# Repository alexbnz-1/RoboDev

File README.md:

# RoboDev

An open-source STM32-based robotics carrier board with integrated WiFi. Plug in power, plug in your motors and sensors — that's it. No breadboard, no stacked breakout boards, no wiring harness.

> **Status:** Schematic substantially complete · PCB layout not yet started

---

## Architecture

RoboDev uses a two-MCU design:

| | |
|---|---|
| **Primary MCU** | STM32G431RBTx · Cortex-M4F 170 MHz · motor control, real-time I/O |
| **WiFi co-processor** | ESP32-C3-MINI-1-N4 · SPI-connected · handles wireless comms |

---

## What's on the board

| | |
|---|---|
| **DC motors** | 4 channels · DRV8874PWPR · up to ~40 V · ~5 A cont. |
| **Servos** | 16 channels · PCA9685PW · 5 V servo rail |
| **Steppers** | 2× NEMA 17 · TMC2209-LA-T · StealthChop2 · silent operation |
| **CAN bus** | SN65HVD230D · ISO 11898-1 · screw terminal + 5.08 mm connector |
| **IMU** | BMI270 · 6-axis accel + gyro · SPI interface |
| **16-bit ADC** | ADS1115IDGST · 4-channel · I²C |
| **Native ADC** | 3× 2.54 mm headers · STM32 ADC |
| **GPIO expander** | PCF8574DW · 8 additional I/O · I²C |
| **Encoders** | 2 channels · 2.54 mm headers |
| **I²C expansion** | 16 independent ports · mix of QWIIC (JST SH) + 2.54 mm · 2× TCA9548APWR mux |
| **USB** | Type-C · USB4085-GF-A |
| **SWD debug** | 2.54 mm header |
| **UART** | 2× headers (debug + general) |
| **Power input** | XT60PW-M · reverse polarity protection · slide switch |

---

## Motor compatibility

| Motor | Works? | Notes |
|---|---|---|
| TT yellow gearmotors (2WD/4WD) | ✓ | Ideal fit |
| Pololu micro/mini gearmotors | ✓ | Well within limits |
| 25–37 mm DC gearmotors | ✓ | Software current limiting recommended near stall |
| Hobby servos | ✓ | Up to 16 channels via PCA9685 |
| NEMA 17 steppers | ✓ | TMC2209 · 2 A RMS / 2.8 A peak |
| CAN motor controllers (VESC, ODrive) | ✓ | Via SN65HVD230D CAN transceiver |
| 775-size / high-current motors | ✗ | Exceeds DRV8874 — use an external driver |

---

## Power

Five independent rails from a single XT60 input with reverse polarity protection (IRF4905 P-channel MOSFET) and a slide switch.

```
XT60  →  IRF4905 (reverse protect)  →  slide switch
           ├── VMOT    adj. buck (XL4016)  →  DC motors
           ├── VSTEP   adj. buck (XL4016)  →  steppers
           ├── +5V     LM2596T-5           →  servo rail + USB
           └── +3V3    AP2112K-3.3 LDO     →  STM32 + ESP32-C3 + all logic
```

VMOT and VSTEP are separate adjustable bucks so DC motors and steppers can run at different voltages simultaneously.

---

## I²C expansion

16 independent I²C ports behind two TCA9548APWR mux ICs — at zero GPIO cost, sharing the existing I²C bus. Each port is an isolated bus segment, so you can connect multiple devices with the same address across different ports without conflict.

3 ports are QWIIC (JST SH), the rest are standard 2.54 mm 4-pin headers. All carry GND / 3.3V / SDA / SCL.

---

## I²C address map

| Address | Device |
|---|---|
| 0x20 | PCF8574DW — digital GPIO expander |
| 0x3C | OLED display (user-supplied, optional) |
| 0x40 | PCA9685PW — 16-channel servo PWM |
| 0x48 | ADS1115IDGST — 16-bit ADC |
| 0x70 | TCA9548A Mux #1 — expansion ports 0–7 |
| 0x71 | TCA9548A Mux #2 — expansion ports 8–15 |

> BMI270 IMU is on SPI (via ESP32-C3), not I²C.

---

## Schematic structure

The KiCad project uses a hierarchical multi-sheet design:

| Sheet | Contents |
|---|---|
| Root | Top-level interconnect, mounting holes |
| `power` | XT60 input, reverse protect, all buck converters, LDO |
| `stm32` | STM32G431RBTx, SN65HVD230D CAN, USB-C, SWD, UART, ADC headers, encoders |
| `spi_bus` | ESP32-C3-MINI-1-N4 WiFi module, BMI270 IMU, 74HC595 shift register |
| `i2c_bus` | TCA9548A ×2 muxes, ADS1115 ADC, PCF8574 GPIO expander, all I²C headers |
| `motor_dc` | DRV8874PWPR ×4, motor output terminals, fault LEDs |
| `motor_stepper` | TMC2209-LA-T ×2, stepper output terminals, UART config |
| `motor_servo` | PCA9685PW, 16-channel servo headers |

---

## Project status

- [x] Design spec complete
- [x] KiCad schematic — substantially complete (all major blocks drawn)
- [ ] PCB layout
- [ ] Bringup firmware (I²C scan, PWM test, CAN loopback, UART echo)
- [ ] TCA9548A reverse-ARP HAL
- [ ] BMI270 driver + sensor fusion
- [ ] TMC2209 UART config
- [ ] Full LCSC/Mouser BOM with pricing

---

## Bill of materials

Key ICs: STM32G431RBTx · ESP32-C3-MINI-1-N4 · DRV8874PWPR ×4 · TMC2209-LA-T ×2 · PCA9685PW · ADS1115IDGST · PCF8574DW · TCA9548APWR ×2 · SN65HVD230D · BMI270 · USB4085-GF-A · XL4016 ×2 · LM2596T-5 · AP2112K-3.3

---

## Repo structure

```
/
├── hardware/
│   └── Robodev/     KiCad project (schematic + PCB)
├── firmware/        ESP-IDF / STM32 firmware (not yet started)
├── docs/
│   ├── Datasheets/  Component datasheets
│   └── RoboDevDesignSpec.docx
└── README.md
```

---

## Contributing

This is an early-stage open hardware project — no PCB has been fabricated yet. If you want to follow along or contribute, the most useful things right now are:

- KiCad schematic review
- Firmware: STM32 HAL bringup, TCA9548A I²C mux driver, TMC2209 UART configuration
- ESP32-C3 SPI bridge firmware
- BMI270 SPI driver + Madgwick/Mahony filter

---

*STM32 + ESP32-C3 Integrated Robotics Carrier Board · May 2026*

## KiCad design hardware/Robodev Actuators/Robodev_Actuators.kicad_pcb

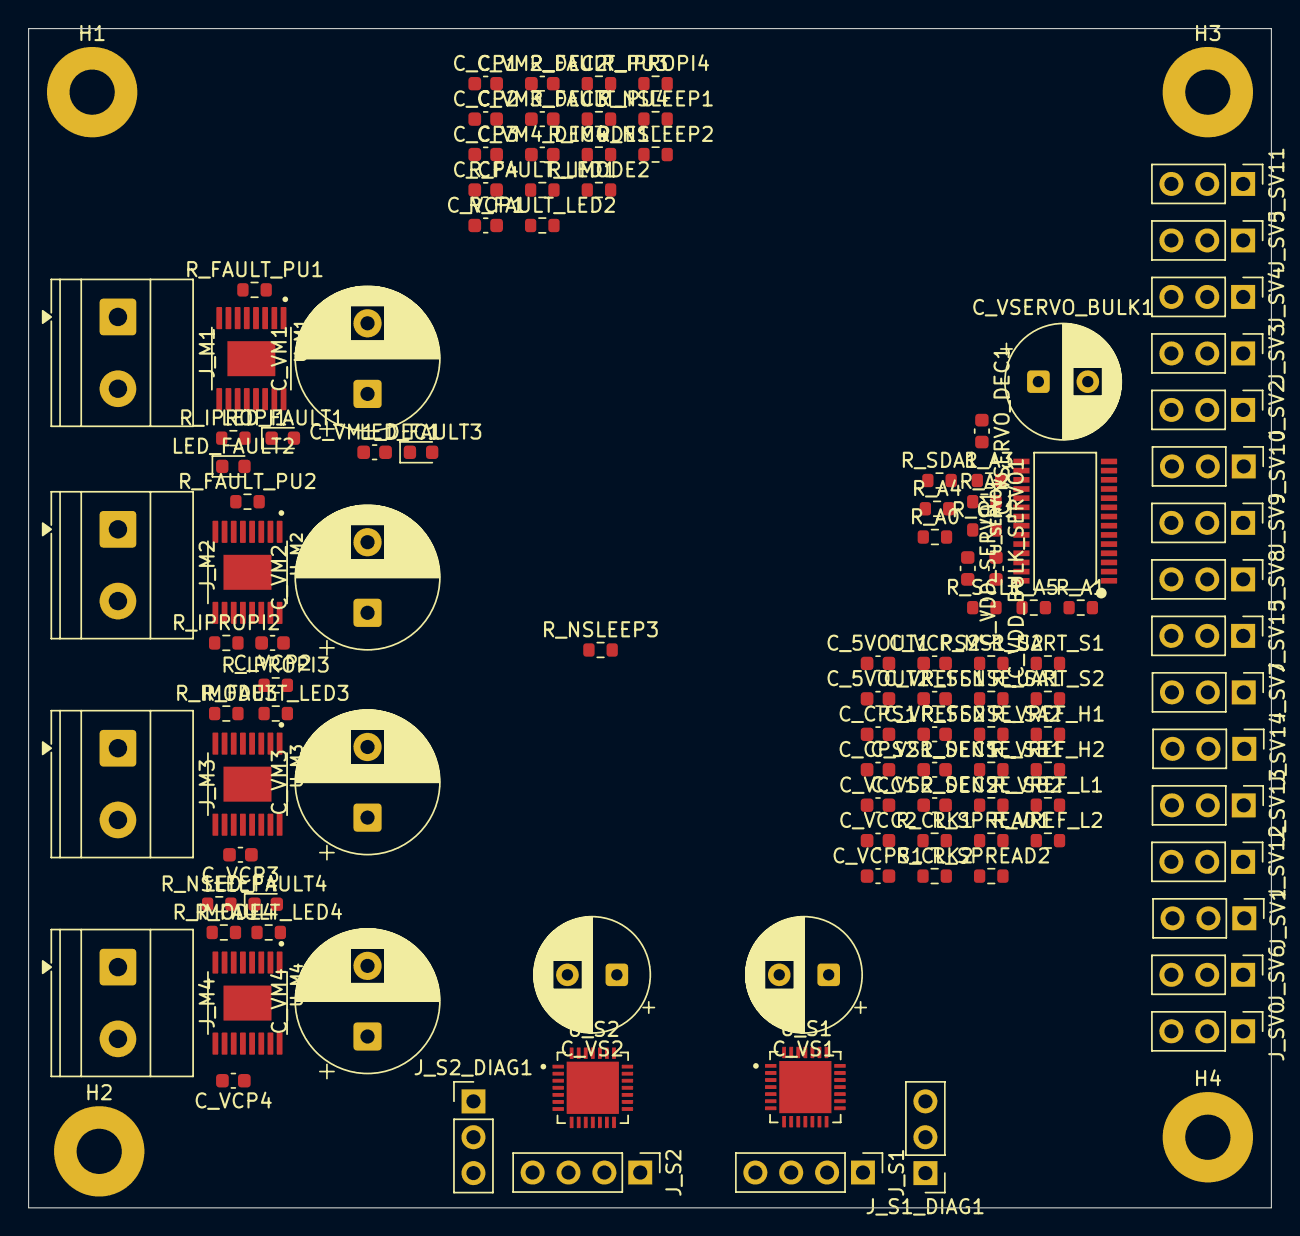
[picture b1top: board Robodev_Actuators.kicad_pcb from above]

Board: 4 copper layers, 88.0 x 83.5 mm, 117 parts (0 on the bottom side), 107 nets, no tracks yet.

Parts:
C_5VOUT1, C_5VOUT2: 4.7 µF 10V X5R; C_0603_1608Metric
C_CP1: 22nF 50V X7R; C_0603_1608Metric
C_CP2, C_CP3, C_CP4: 22 nF 50V X7R; C_0603_1608Metric
C_CPS1, C_CPS2: 100 nF 50V X7R; C_0603_1608Metric
C_VCC1, C_VCC2: 100 nF 10V X7R; C_0603_1608Metric
C_VCP1, C_VCP2, C_VCP3, C_VCP4: 100 nF 50V X7R; C_0603_1608Metric
C_VCPS1, C_VCPS2: 100 nF 50V X7R; C_0603_1608Metric
C_VDD_BULK_SERVO1: 10 µF 10V X5R; C_0603_1608Metric
C_VDD_SERVO1: 100 nF 10V X7R; C_0603_1608Metric
C_VM1, C_VM2, C_VM3, C_VM4: 470 µF 50V electrolytic; CP_Radial_D10.0mm_P5.00mm
C_VM1_DEC1, C_VM2_DEC2, C_VM3_DEC3, C_VM4_DEC4: 100 nF 50V X7R; C_0603_1608Metric
C_VREFS1, C_VREFS2: 100 nF 10V X7R; C_0603_1608Metric
C_VS1, C_VS2: 100 µF 50V electrolytic; CP_Radial_D8.0mm_P3.50mm
C_VS1_DEC1, C_VS2_DEC2: 100 nF 50V X7R; C_0603_1608Metric
C_VSERVO_BULK1: 220 µF 25V electrolytic; CP_Radial_D8.0mm_P3.50mm
C_VSERVO_DEC1: 100 nF 50V X7R; C_0603_1608Metric
H1, H2, H3, H4: MountingHole_Pad; MountingHole_3.2mm_M3_Pad
J_M1, J_M2, J_M3, J_M4: Conn_01x02; TerminalBlock_Phoenix_MKDS-1,5-2-5.08_1x02_P5.08mm_Horizont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
J_S1, J_S2: Stepper 4-pin 2.54mm; PinHeader_1x04_P2.54mm_Vertical
J_S1_DIAG1: Stepper 1 DIAG/INDEX; PinHeader_1x03_P2.54mm_Vertical
J_S2_DIAG1: Stepper 2 DIAG/INDEX; PinHeader_1x03_P2.54mm_Vertical
J_SV0, J_SV1, J_SV2, J_SV3, J_SV4, J_SV5, J_SV6, J_SV7, J_SV8, J_SV9, J_SV10, J_SV11, J_SV12, J_SV13, J_SV14, J_SV15: Conn_01x03; PinHeader_1x03_P2.54mm_Vertical
LED_FAULT1, LED_FAULT2, LED_FAULT3, LED_FAULT4: LTST-C190KRKT Red; LED_0603_1608Metric
R_A0, R_A1, R_A2, R_A3, R_A4, R_A5: 100 kΩ 1% 0603; R_0603_1608Metric
R_CLK1, R_CLK2: 100 kΩ 1% 0603; R_0603_1608Metric
R_FAULT_LED1, R_FAULT_LED2, R_FAULT_LED3, R_FAULT_LED4: 1 kΩ 1% 0603; R_0603_1608Metric
R_FAULT_PU1, R_FAULT_PU2, R_FAULT_PU3, R_FAULT_PU4: 10 kΩ 1% 0603; R_0603_1608Metric
R_IMODE1, R_IMODE2, R_IMODE3, R_IMODE4: 20 kΩ 1% 0603; R_0603_1608Metric
R_IPROPI1, R_IPROPI2, R_IPROPI3, R_IPROPI4: 1 kΩ 1% 0603; R_0603_1608Metric
R_MS1_S2: 10 kΩ 1% 0603; R_0603_1608Metric
R_NSLEEP1, R_NSLEEP2, R_NSLEEP3, R_NSLEEP4: 100 kΩ 1% 0603; R_0603_1608Metric
R_OE1: 100 kΩ 1% 0603; R_0603_1608Metric
R_SCL1: 4.7 kΩ 1% 0603; R_0603_1608Metric
R_SDA1: 4.7 kΩ 1% 0603; R_0603_1608Metric
R_SENSE_SA1, R_SENSE_SA2: 100 mΩ 1% 0603; R_0603_1608Metric
R_SENSE_SB1, R_SENSE_SB2: 100 mΩ 1% 0603; R_0603_1608Metric
R_SPREAD1, R_SPREAD2: 100 kΩ 1% 0603; R_0603_1608Metric
R_UART_S1, R_UART_S2: 1 kΩ 1% 0603; R_0603_1608Metric
R_VREF_H1, R_VREF_H2: 10 kΩ 1% 0603; R_0603_1608Metric
R_VREF_L1, R_VREF_L2: 27 kΩ 1% 0603; R_0603_1608Metric
U_M1, U_M2, U_M3, U_M4: DRV8874PWPR; SOP65P640X120-17N
U_S1, U_S2: TMC2209-LA-T; QFN50P500X500X90-29N
U_SERVO1: PCA9685PW; TSSOP28-0.65-9.7X4.4MM

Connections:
+3V3: C_VCC1.2, C_VCC2.2, C_VDD_BULK_SERVO1.2, C_VDD_SERVO1.2, R_FAULT_PU1.1, R_FAULT_PU2.1, R_FAULT_PU3.1, R_FAULT_PU4.1, R_MS1_S2.1, R_NSLEEP1.1, R_NSLEEP2.1, R_NSLEEP3.1, R_NSLEEP4.1, R_SCL1.1, R_SDA1.1, R_VREF_H1.1, R_VREF_H2.1, U_M1.5 (VREF), U_M2.5 (VREF), U_M3.5 (VREF), U_M4.5 (VREF), U_S1.15 (VCC_IO), U_S2.15 (VCC_IO), U_SERVO1.28 (VDD)
/motor_dc/IPROPI_M1: R_IPROPI1.1, U_M1.6 (IPROPI)
/motor_dc/IPROPI_M2: R_IPROPI2.1, U_M2.6 (IPROPI)
/motor_dc/IPROPI_M3: R_IPROPI3.1, U_M3.6 (IPROPI)
/motor_dc/IPROPI_M4: R_IPROPI4.1, U_M4.6 (IPROPI)
/motor_dc/VMOT: C_VCP1.2, C_VCP2.2, C_VCP3.2, C_VCP4.2, C_VM1.1, C_VM1_DEC1.1, C_VM2.1, C_VM2_DEC2.1, C_VM3.1, C_VM3_DEC3.1, C_VM4.1, C_VM4_DEC4.1, U_M1.11 (VM), U_M2.11 (VM), U_M3.11 (VM), U_M4.11 (VM)
/motor_servo/I2C_SCL: R_SCL1.2, U_SERVO1.26 (SCL)
/motor_servo/I2C_SDA: R_SDA1.2, U_SERVO1.27 (SDA)
/motor_servo/SV_PWM0: J_SV0.3, U_SERVO1.6 (LED0)
/motor_servo/SV_PWM1: J_SV1.3, U_SERVO1.7 (LED1)
/motor_servo/SV_PWM2: J_SV2.3, U_SERVO1.8 (LED2)
/motor_servo/SV_PWM3: J_SV3.3, U_SERVO1.9 (LED3)
/motor_servo/SV_PWM4: J_SV4.3, U_SERVO1.10 (LED4)
/motor_servo/SV_PWM5: J_SV5.3, U_SERVO1.11 (LED5)
/motor_servo/SV_PWM6: J_SV6.3, U_SERVO1.12 (LED6)
/motor_servo/SV_PWM7: J_SV7.3, U_SERVO1.13 (LED7)
/motor_servo/SV_PWM8: J_SV8.3, U_SERVO1.15 (LED8)
/motor_servo/SV_PWM9: J_SV9.3, U_SERVO1.16 (LED9)
/motor_servo/SV_PWM10: J_SV10.3, U_SERVO1.17 (LED10)
/motor_servo/SV_PWM11: J_SV11.3, U_SERVO1.18 (LED11)
/motor_servo/SV_PWM12: J_SV12.3, U_SERVO1.19 (LED12)
/motor_servo/SV_PWM13: J_SV13.3, U_SERVO1.20 (LED13)
/motor_servo/SV_PWM14: J_SV14.3, U_SERVO1.21 (LED14)
/motor_servo/SV_PWM15: J_SV15.3, U_SERVO1.22 (LED15)
/motor_stepper/S1_VREF: C_VREFS1.1, R_VREF_H1.2, R_VREF_L1.1, U_S1.17 (VREF)
/motor_stepper/S2_VREF: C_VREFS2.1, R_VREF_H2.2, R_VREF_L2.1, U_S2.17 (VREF)
/motor_stepper/TMC_UART: R_UART_S1.1, R_UART_S2.1
GND: C_5VOUT1.2, C_5VOUT2.2, C_VCC1.1, C_VCC2.1, C_VDD_BULK_SERVO1.1, C_VDD_SERVO1.1, C_VM1.2, C_VM1_DEC1.2, C_VM2.2, C_VM2_DEC2.2, C_VM3.2, C_VM3_DEC3.2, C_VM4.2, C_VM4_DEC4.2, C_VREFS1.2, C_VREFS2.2, H1.1, H2.1, H3.1, H4.1, J_S1_DIAG1.1, J_S2_DIAG1.1, LED_FAULT1.1 (K), LED_FAULT2.1 (K), LED_FAULT3.1 (K), LED_FAULT4.1 (K), R_A0.1, R_A1.1, R_A2.1, R_A3.1, R_A4.1, R_A5.1, R_CLK1.1, R_CLK2.1, R_IMODE1.1, R_IMODE2.1, R_IMODE3.1, R_IMODE4.1, R_IPROPI1.2, R_IPROPI2.2, R_IPROPI3.2, R_IPROPI4.2, R_OE1.1, R_SPREAD1.1, R_SPREAD2.1, R_VREF_L1.2, R_VREF_L2.2, U_M1.16 (PMODE), U_M2.16 (PMODE), U_M3.16 (PMODE), U_M4.16 (PMODE), U_S1.9 (MS1_AD0), U_S1.10 (MS2_AD1), U_S2.10 (MS2_AD1), U_SERVO1.14 (VSS), U_SERVO1.25 (EXTCLK)
MGND: U_M1.9 (PGND), U_M1.15 (GND), U_M2.9 (PGND), U_M2.15 (GND), U_M3.9 (PGND), U_M3.15 (GND), U_M4.9 (PGND), U_M4.15 (GND)
unnamed: J_M1.1, U_M1.8 (OUT1)
unnamed: J_M1.2, U_M1.10 (OUT2)
unnamed: J_M2.1, U_M2.8 (OUT1)
unnamed: J_M2.2, U_M2.10 (OUT2)
unnamed: J_M3.1, U_M3.8 (OUT1)
unnamed: J_M3.2, U_M3.10 (OUT2)
unnamed: J_M4.1, U_M4.8 (OUT1)
unnamed: J_M4.2, U_M4.10 (OUT2)
unnamed: J_S1.1, U_S1.24 (OA1)
unnamed: J_S1.2, U_S1.21 (OA2)
unnamed: J_S1.3, U_S1.26 (OB1)
unnamed: J_S1.4, U_S1.1 (OB2)
unnamed: J_S1_DIAG1.2, U_S1.11 (DIAG)
unnamed: J_S1_DIAG1.3, U_S1.12 (INDEX)
unnamed: J_S2.1, U_S2.24 (OA1)
unnamed: J_S2.2, U_S2.21 (OA2)
unnamed: J_S2.3, U_S2.26 (OB1)
unnamed: J_S2.4, U_S2.1 (OB2)
unnamed: J_S2_DIAG1.2, U_S2.11 (DIAG)
unnamed: J_S2_DIAG1.3, U_S2.12 (INDEX)
unnamed: LED_FAULT1.2 (A), R_FAULT_LED1.2
unnamed: LED_FAULT2.2 (A), R_FAULT_LED2.2
unnamed: LED_FAULT3.2 (A), R_FAULT_LED3.2
unnamed: LED_FAULT4.2 (A), R_FAULT_LED4.2
unnamed: C_CP1.1, U_M1.13 (CPH)
unnamed: C_CP1.2, U_M1.14 (CPL)
unnamed: R_IMODE1.2, U_M1.7 (IMODE)
unnamed: R_FAULT_LED1.1, R_FAULT_PU1.2, U_M1.4 (NFAULT)
unnamed: R_NSLEEP1.2, U_M1.3 (NSLEEP)
unnamed: C_VCP1.1, U_M1.12 (VCP)
unnamed: C_CP2.1, U_M2.13 (CPH)
unnamed: C_CP2.2, U_M2.14 (CPL)
unnamed: R_IMODE2.2, U_M2.7 (IMODE)
unnamed: R_FAULT_LED2.1, R_FAULT_PU2.2, U_M2.4 (NFAULT)
unnamed: R_NSLEEP2.2, U_M2.3 (NSLEEP)
unnamed: C_VCP2.1, U_M2.12 (VCP)
unnamed: C_CP3.1, U_M3.13 (CPH)
unnamed: C_CP3.2, U_M3.14 (CPL)
unnamed: R_IMODE3.2, U_M3.7 (IMODE)
unnamed: R_FAULT_LED3.1, R_FAULT_PU3.2, U_M3.4 (NFAULT)
unnamed: R_NSLEEP3.2, U_M3.3 (NSLEEP)
unnamed: C_VCP3.1, U_M3.12 (VCP)
unnamed: C_CP4.1, U_M4.13 (CPH)
unnamed: C_CP4.2, U_M4.14 (CPL)
unnamed: R_IMODE4.2, U_M4.7 (IMODE)
unnamed: R_FAULT_LED4.1, R_FAULT_PU4.2, U_M4.4 (NFAULT)
unnamed: R_NSLEEP4.2, U_M4.3 (NSLEEP)
unnamed: C_VCP4.1, U_M4.12 (VCP)
unnamed: C_5VOUT1.1, U_S1.8 (5VOUT)
unnamed: R_SENSE_SA1.1, U_S1.23 (BRA)
unnamed: R_SENSE_SB1.1, U_S1.27 (BRB)
unnamed: R_CLK1.2, U_S1.13 (CLK)
unnamed: C_CPS1.1, U_S1.5 (CPI)
unnamed: C_CPS1.2, U_S1.4 (CPO)
unnamed: R_SPREAD1.2, U_S1.7 (SPREAD)
unnamed: C_VCPS1.1, U_S1.6 (VCP)
unnamed: R_UART_S1.2, U_S1.14 (~PD_UART)
unnamed: C_5VOUT2.1, U_S2.8 (5VOUT)
unnamed: R_SENSE_SA2.1, U_S2.23 (BRA)
unnamed: R_SENSE_SB2.1, U_S2.27 (BRB)
unnamed: R_CLK2.2, U_S2.13 (CLK)
unnamed: C_CPS2.1, U_S2.5 (CPI)
unnamed: C_CPS2.2, U_S2.4 (CPO)
unnamed: R_MS1_S2.2, U_S2.9 (MS1_AD0)
unnamed: R_SPREAD2.2, U_S2.7 (SPREAD)
unnamed: C_VCPS2.1, U_S2.6 (VCP)
unnamed: R_UART_S2.2, U_S2.14 (~PD_UART)
unnamed: R_A0.2, U_SERVO1.1 (A0)
unnamed: R_A1.2, U_SERVO1.2 (A1)
unnamed: R_A2.2, U_SERVO1.3 (A2)
unnamed: R_A3.2, U_SERVO1.4 (A3)
unnamed: R_A4.2, U_SERVO1.5 (A4)
unnamed: R_A5.2, U_SERVO1.24 (A5)
unnamed: R_OE1.2, U_SERVO1.23 (~OE)
SERVOGND: C_VSERVO_BULK1.2, C_VSERVO_DEC1.2, J_SV0.1, J_SV1.1, J_SV2.1, J_SV3.1, J_SV4.1, J_SV5.1, J_SV6.1, J_SV7.1, J_SV8.1, J_SV9.1, J_SV10.1, J_SV11.1, J_SV12.1, J_SV13.1, J_SV14.1, J_SV15.1
STEPGND: C_VCPS1.2, C_VCPS2.2, C_VS1.2, C_VS1_DEC1.1, C_VS2.2, C_VS2_DEC2.1, R_SENSE_SA1.2, R_SENSE_SA2.2, R_SENSE_SB1.2, R_SENSE_SB2.2, U_S1.3 (GND), U_S2.3 (GND)
VS: C_VS1.1, C_VS1_DEC1.2, C_VS2.1, C_VS2_DEC2.2, U_S1.22 (VS), U_S1.28 (VS), U_S2.22 (VS), U_S2.28 (VS)
VSERVO: C_VSERVO_BULK1.1, C_VSERVO_DEC1.1, J_SV0.2, J_SV1.2, J_SV2.2, J_SV3.2, J_SV4.2, J_SV5.2, J_SV6.2, J_SV7.2, J_SV8.2, J_SV9.2, J_SV10.2, J_SV11.2, J_SV12.2, J_SV13.2, J_SV14.2, J_SV15.2

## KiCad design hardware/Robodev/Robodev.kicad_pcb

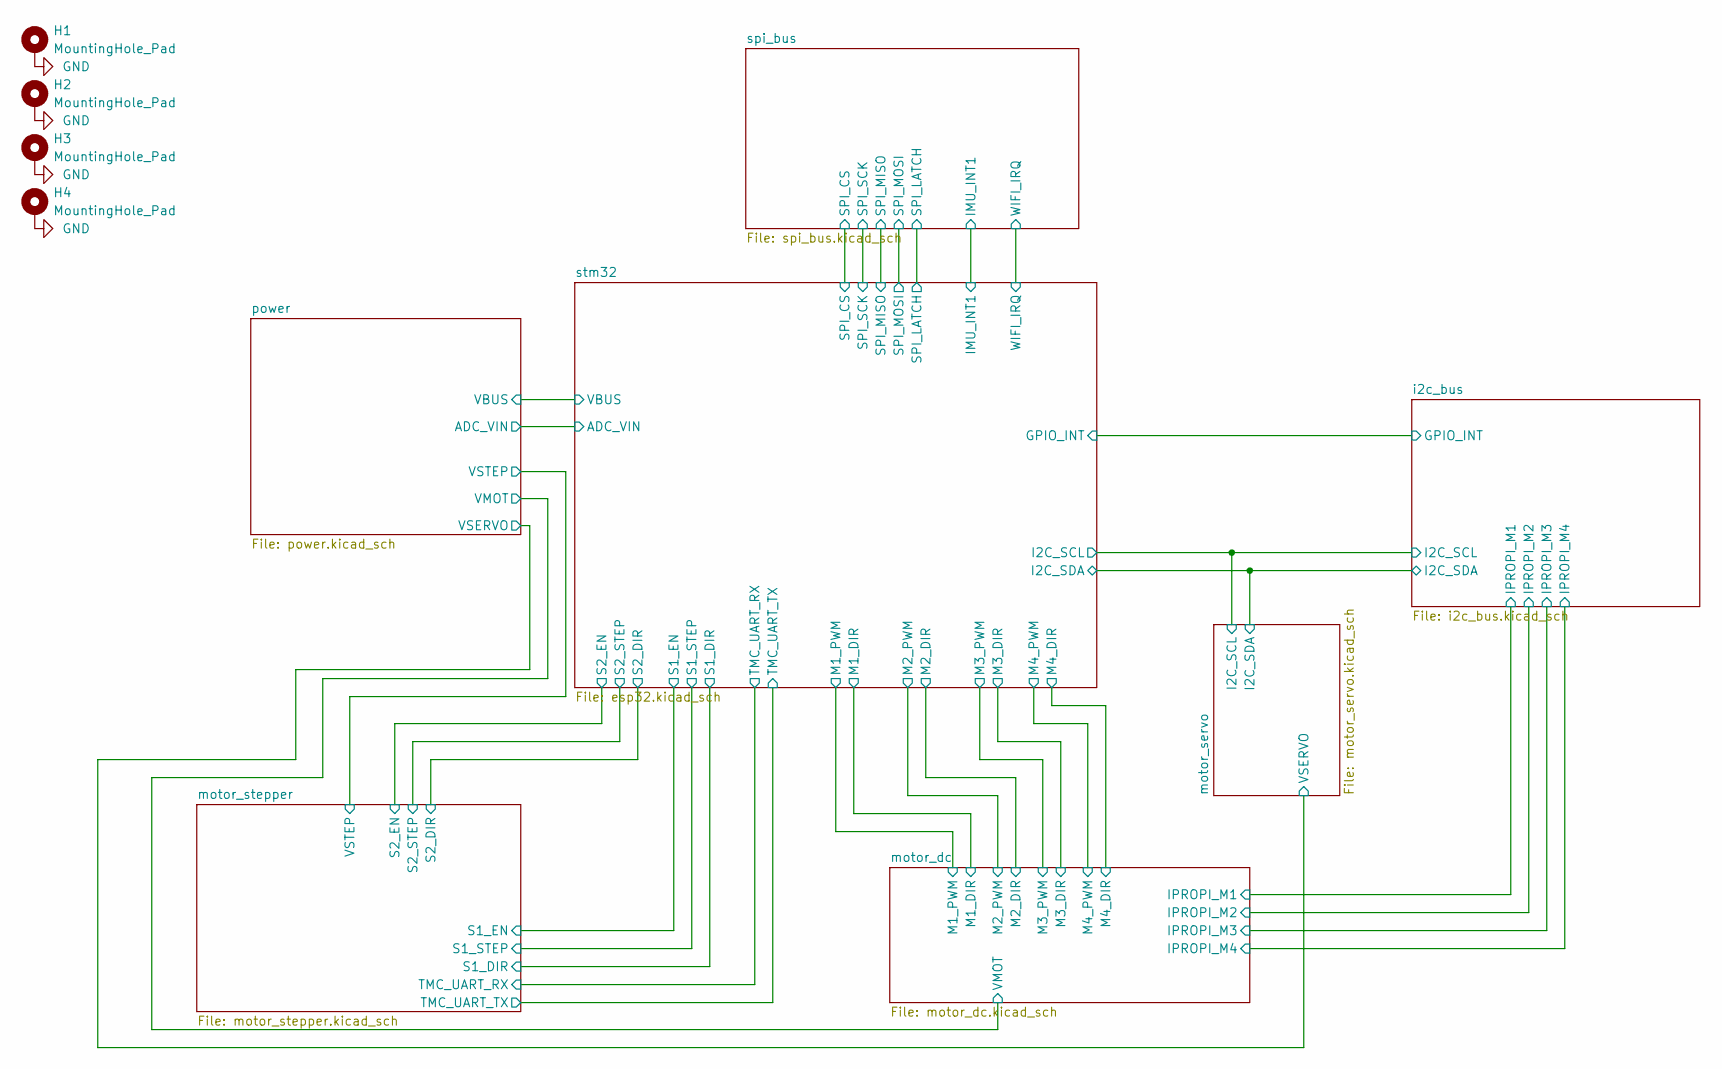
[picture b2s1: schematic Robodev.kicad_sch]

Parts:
H1, H2, H3, H4: MountingHole_Pad; MountingHole_3.2mm_M3_Pad

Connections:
GND: H1.1, H2.1, H3.1, H4.1; also elsewhere on the board

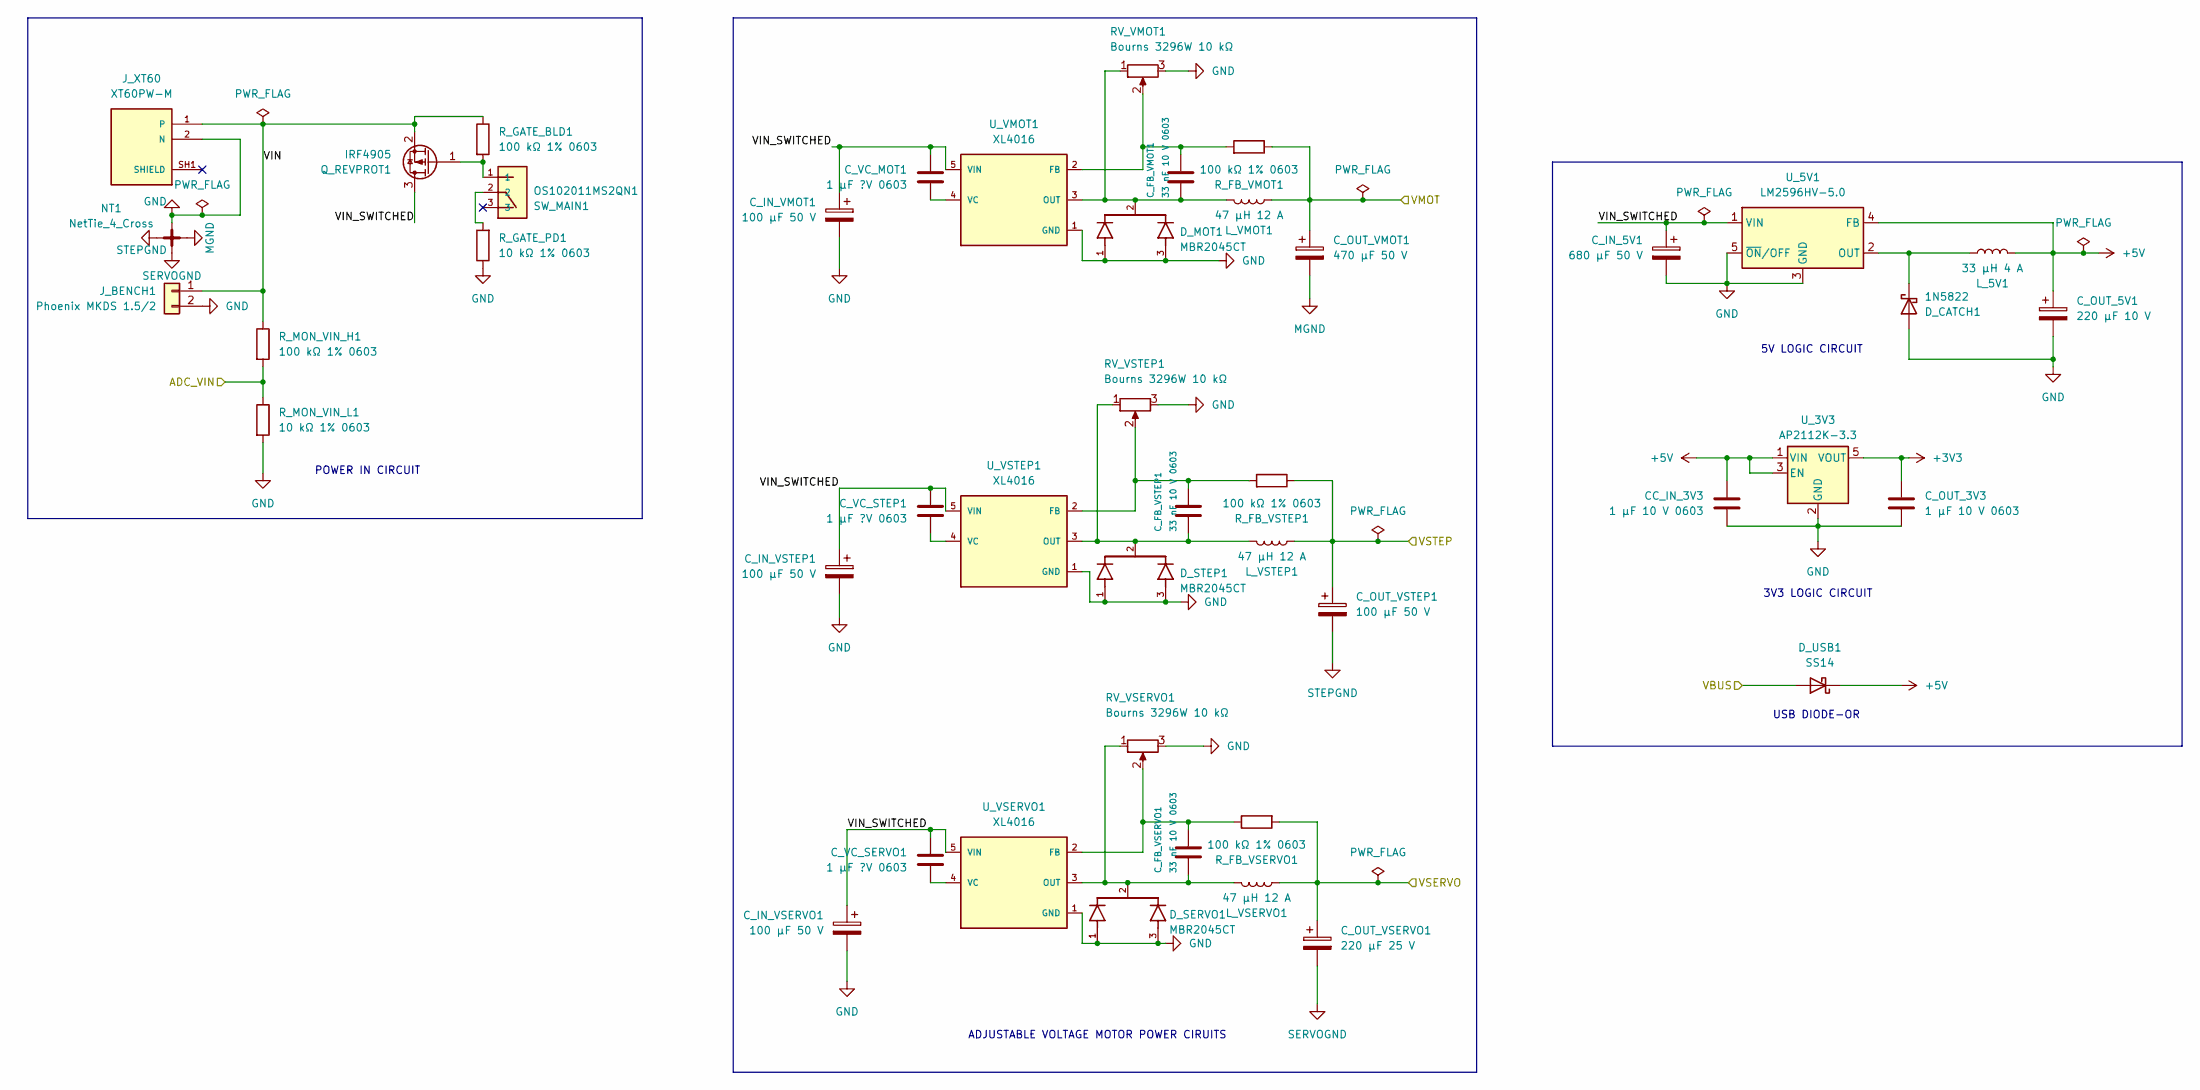
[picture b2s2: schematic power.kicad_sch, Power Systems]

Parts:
CC_IN_3V3: 1 µF 10 V 0603; C_0603_1608Metric
C_FB_VMOT1: 33 nF 10 V 0603; C_0603_1608Metric
C_FB_VSERVO1: 33 nF 10 V 0603; C_0603_1608Metric
C_FB_VSTEP1: 33 nF 10 V 0603; C_0603_1608Metric
C_IN_5V1: 680 µF 50 V; CP_Radial_D12.5mm_P5.00mm
C_IN_VMOT1: 100 µF 50 V; CP_Radial_D10.0mm_P5.00mm
C_IN_VSERVO1: 100 µF 50 V; CP_Radial_D10.0mm_P5.00mm
C_IN_VSTEP1: 100 µF 50 V; CP_Radial_D10.0mm_P5.00mm
C_OUT_3V3: 1 µF 10 V 0603; C_0603_1608Metric
C_OUT_5V1: 220 µF 10 V; CP_Radial_D8.0mm_P3.50mm
C_OUT_VMOT1: 470 µF 50 V; CP_Radial_D12.5mm_P5.00mm
C_OUT_VSERVO1: 220 µF 25 V; CP_Radial_D8.0mm_P3.50mm
C_OUT_VSTEP1: 100 µF 50 V; CP_Radial_D10.0mm_P5.00mm
C_VC_MOT1: 1 µF ?V 0603; C_0603_1608Metric
C_VC_SERVO1: 1 µF ?V 0603; C_0603_1608Metric
C_VC_STEP1: 1 µF ?V 0603; C_0603_1608Metric
D_CATCH1: 1N5822; D_DO-201AD_P12.70mm_Horizontal
D_MOT1: MBR2045CT; TO254P1050X476X2020-3; PARTREV G2104
D_SERVO1: MBR2045CT; TO254P1050X476X2020-3; PARTREV G2104
D_STEP1: MBR2045CT; TO254P1050X476X2020-3; PARTREV G2104
D_USB1: SS14; D_SMA
J_BENCH1: Phoenix MKDS 1.5/2; TerminalBlock_Phoenix_MKDS-1,5-2-5.08_1x02_P5.08mm_Horizont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
J_XT60: XT60PW-M; AMASS_XT60PW-M; PARTREV 1.2
L_5V1: 33 µH 4 A; L_Radial_D10.0mm_P5.00mm_Fastron_07M
L_VMOT1: 47 µH 12 A; L_Radial_D10.0mm_P5.00mm_Fastron_07M
L_VSERVO1: 47 µH 12 A; L_Radial_D10.0mm_P5.00mm_Fastron_07M
L_VSTEP1: 47 µH 12 A; L_Radial_D10.0mm_P5.00mm_Fastron_07M
NT1: NetTie_4_Cross; NetTie-4_SMD_Pad2.0mm
Q_REVPROT1: IRF4905; TO-220-3_Vertical
RV_VMOT1: Bourns 3296W 10 kΩ; Potentiometer_Bourns_3296W_Vertical
RV_VSERVO1: Bourns 3296W 10 kΩ; Potentiometer_Bourns_3296W_Vertical
RV_VSTEP1: Bourns 3296W 10 kΩ; Potentiometer_Bourns_3296W_Vertical
R_FB_VMOT1: 100 kΩ 1% 0603; R_0603_1608Metric
R_FB_VSERVO1: 100 kΩ 1% 0603; R_0603_1608Metric
R_FB_VSTEP1: 100 kΩ 1% 0603; R_0603_1608Metric
R_GATE_BLD1: 100 kΩ 1% 0603; R_0603_1608Metric
R_GATE_PD1: 10 kΩ 1% 0603; R_0603_1608Metric
R_MON_VIN_H1: 100 kΩ 1% 0603; R_0603_1608Metric
R_MON_VIN_L1: 10 kΩ 1% 0603; R_0603_1608Metric
SW_MAIN1: OS102011MS2QN1; SW_OS102011MS2QN1
U_3V3: AP2112K-3.3; SOT-23-5_HandSoldering
U_5V1: LM2596HV-5.0; TO-263-5_TabPin3
U_VMOT1: XL4016; LM2576T2
U_VSERVO1: XL4016; LM2576T2
U_VSTEP1: XL4016; LM2576T2

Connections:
+3V3: C_OUT_3V3.1, U_3V3.5 (VOUT); also elsewhere on the board
+5V: CC_IN_3V3.1, C_OUT_5V1.1, D_USB1.1 (K), L_5V1.1, U_3V3.1 (VIN), U_3V3.3 (EN), U_5V1.4 (FB)
/motor_dc/VMOT: C_OUT_VMOT1.1, L_VMOT1.2, R_FB_VMOT1.1; also elsewhere on the board
/power/ADC_VIN: R_MON_VIN_H1.2, R_MON_VIN_L1.1; also elsewhere on the board
/power/VIN: J_BENCH1.1, J_XT60.1, Q_REVPROT1.2 (S), R_GATE_BLD1.1, R_MON_VIN_H1.1
/power/VIN_SWITCHED: C_IN_5V1.1, C_IN_VMOT1.1, C_IN_VSERVO1.1, C_IN_VSTEP1.1, C_VC_MOT1.1, C_VC_SERVO1.1, C_VC_STEP1.1, Q_REVPROT1.3 (D), U_5V1.1 (VIN), U_VMOT1.5 (VIN), U_VSERVO1.5 (VIN), U_VSTEP1.5 (VIN)
GND: CC_IN_3V3.2, C_IN_5V1.2, C_IN_VMOT1.2, C_IN_VSERVO1.2, C_IN_VSTEP1.2, C_OUT_3V3.2, C_OUT_5V1.2, D_CATCH1.2 (A), D_MOT1.1, D_MOT1.3, D_SERVO1.1, D_SERVO1.3, D_STEP1.1, D_STEP1.3, J_BENCH1.2, J_XT60.2 (N), NT1.3, RV_VMOT1.3, RV_VSERVO1.3, RV_VSTEP1.3, R_GATE_PD1.1, R_MON_VIN_L1.2, U_3V3.2 (GND), U_5V1.3 (GND), U_5V1.5 (~ON/OFF), U_VMOT1.1 (GND), U_VSERVO1.1 (GND), U_VSTEP1.1 (GND); also elsewhere on the board
MGND: C_OUT_VMOT1.2, NT1.1; also elsewhere on the board
unnamed: D_CATCH1.1 (K), L_5V1.2, U_5V1.2 (OUT)
unnamed: Q_REVPROT1.1 (G), R_GATE_BLD1.2, SW_MAIN1.1
unnamed: R_GATE_PD1.2, SW_MAIN1.2
unnamed: C_FB_VMOT1.2, RV_VMOT1.2, R_FB_VMOT1.2, U_VMOT1.2 (FB)
unnamed: C_FB_VMOT1.1, D_MOT1.2, L_VMOT1.1, RV_VMOT1.1, U_VMOT1.3 (OUT)
unnamed: C_VC_MOT1.2, U_VMOT1.4 (VC)
unnamed: C_FB_VSERVO1.2, RV_VSERVO1.2, R_FB_VSERVO1.1, U_VSERVO1.2 (FB)
unnamed: C_FB_VSERVO1.1, D_SERVO1.2, L_VSERVO1.1, RV_VSERVO1.1, U_VSERVO1.3 (OUT)
unnamed: C_VC_SERVO1.2, U_VSERVO1.4 (VC)
unnamed: C_FB_VSTEP1.2, RV_VSTEP1.2, R_FB_VSTEP1.2, U_VSTEP1.2 (FB)
unnamed: C_FB_VSTEP1.1, D_STEP1.2, L_VSTEP1.2, RV_VSTEP1.1, U_VSTEP1.3 (OUT)
unnamed: C_VC_STEP1.2, U_VSTEP1.4 (VC)
SERVOGND: C_OUT_VSERVO1.2, NT1.4; also elsewhere on the board
STEPGND: C_OUT_VSTEP1.2, NT1.2; also elsewhere on the board
VBUS: D_USB1.2 (A); also elsewhere on the board
VS: C_OUT_VSTEP1.1, L_VSTEP1.1, R_FB_VSTEP1.1; also elsewhere on the board
VSERVO: C_OUT_VSERVO1.1, L_VSERVO1.2, R_FB_VSERVO1.2; also elsewhere on the board

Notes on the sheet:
USB DIODE-OR
3V3 LOGIC CIRCUIT
5V LOGIC CIRCUIT
POWER IN CIRCUIT
ADJUSTABLE VOLTAGE MOTOR POWER CIRUITS

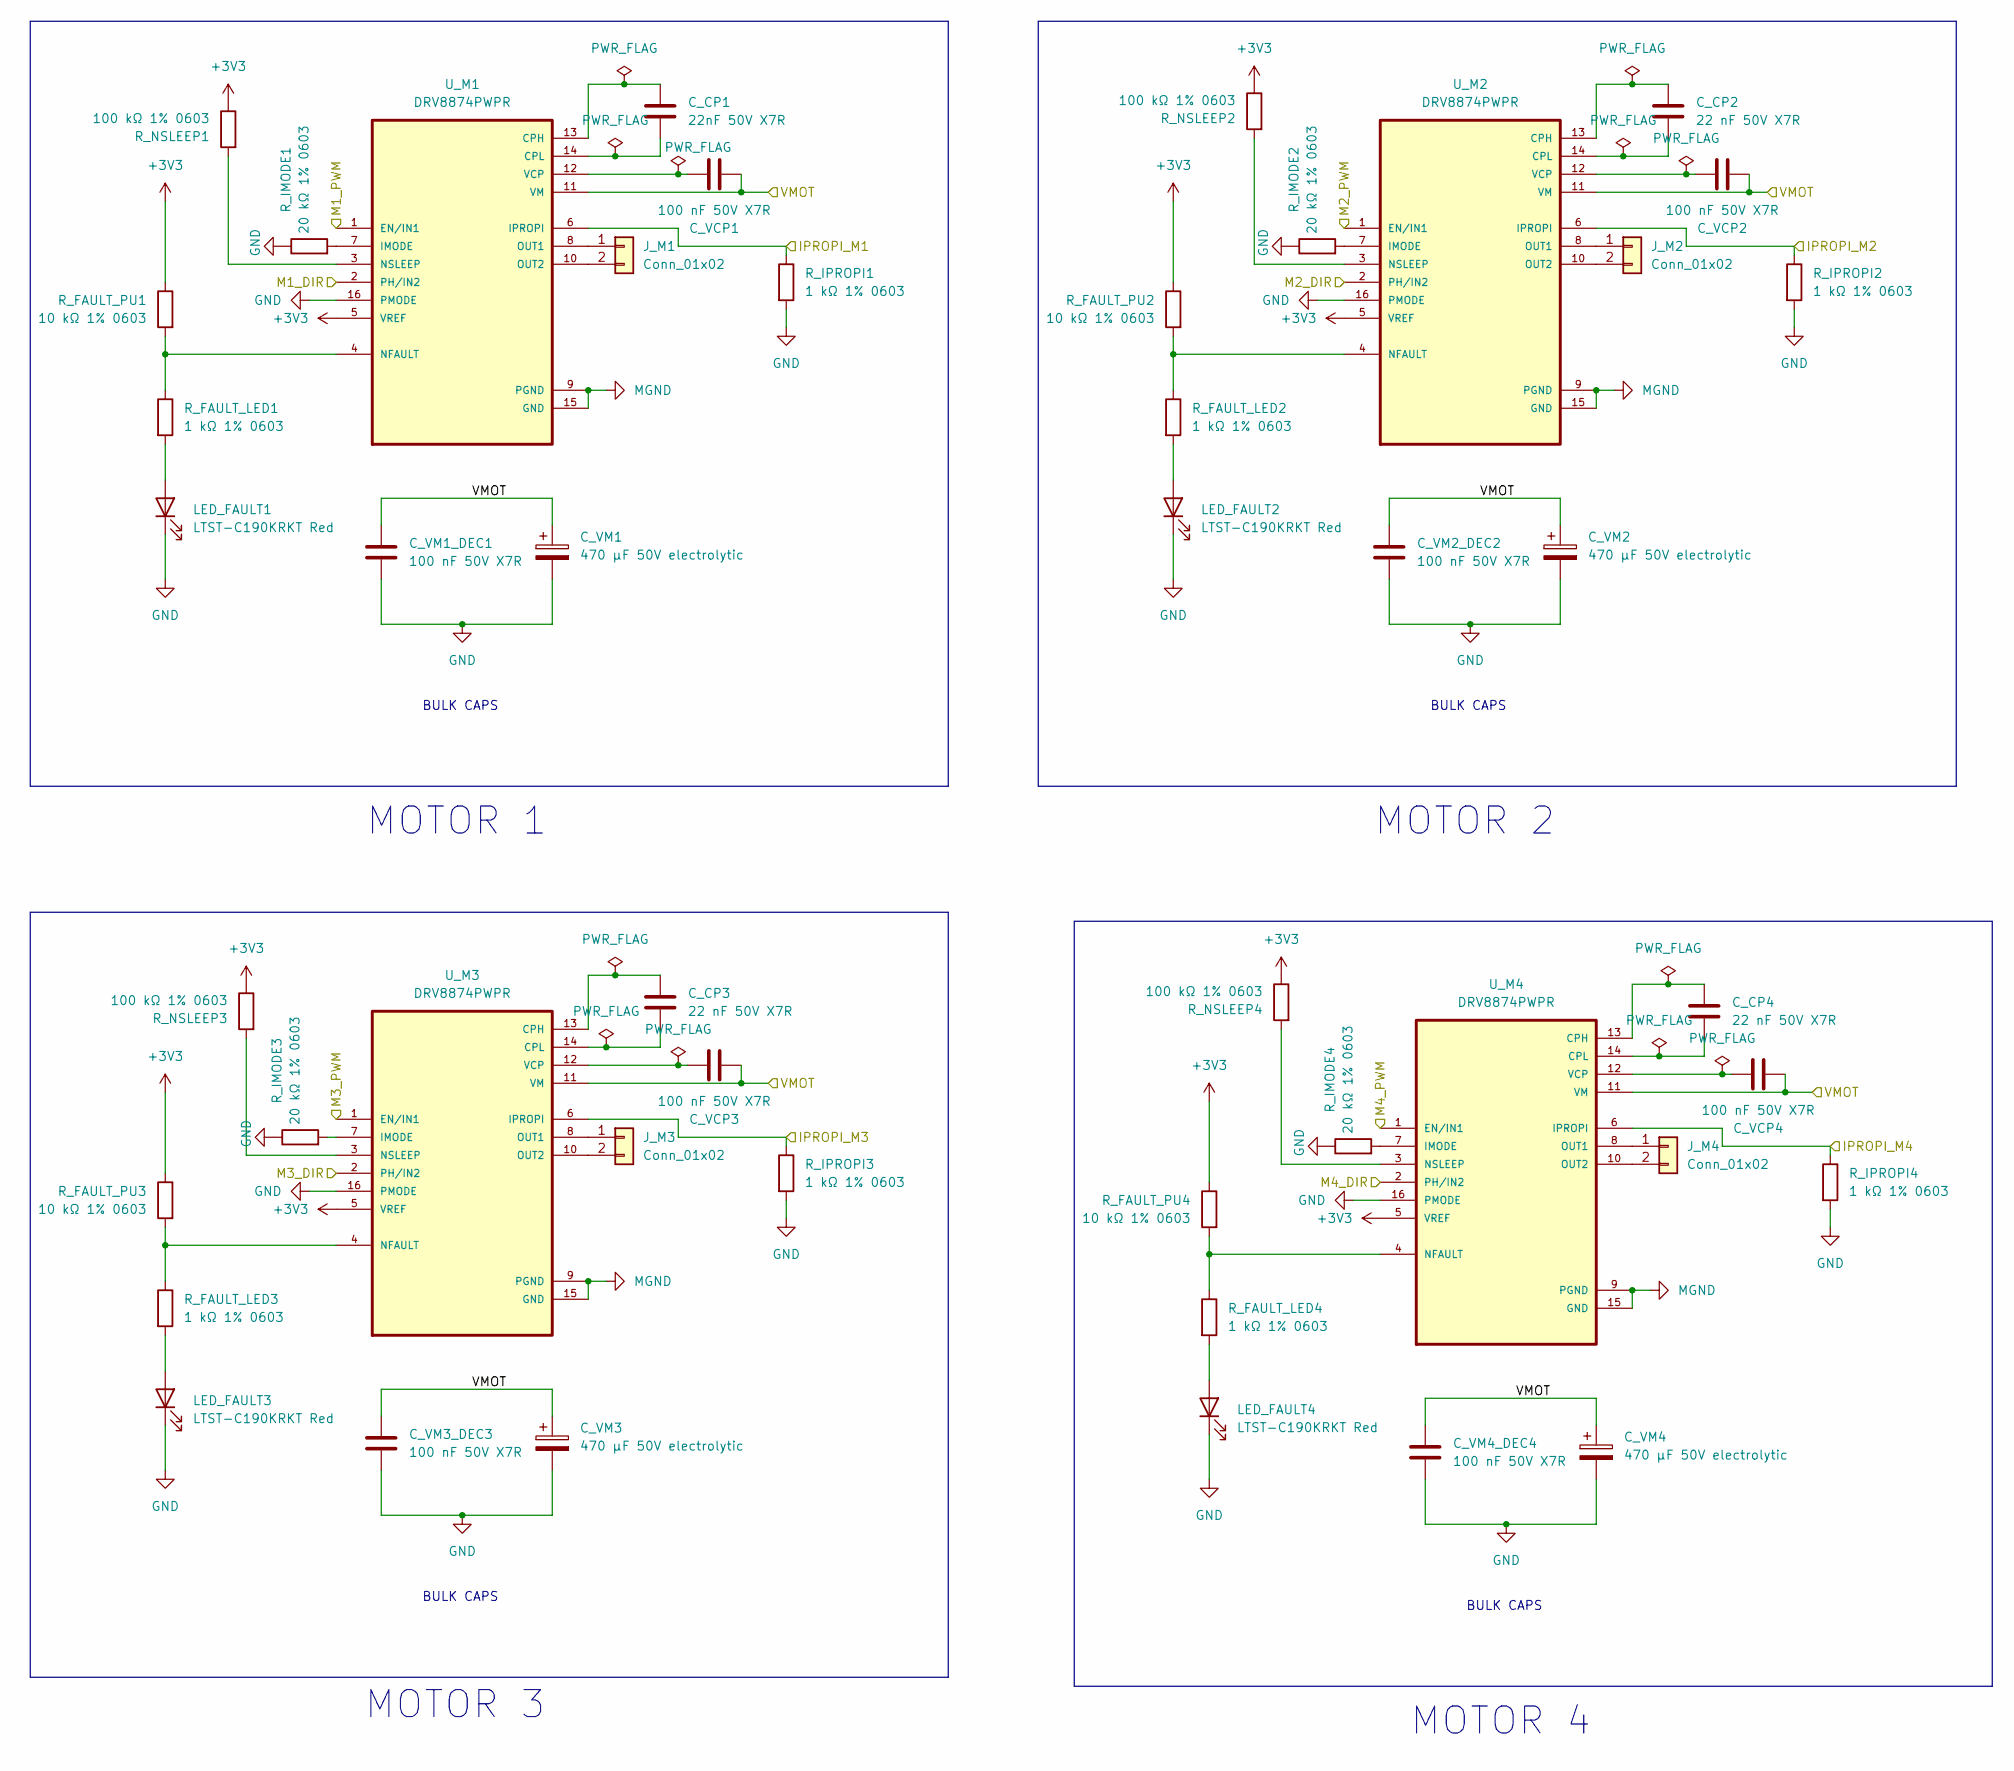
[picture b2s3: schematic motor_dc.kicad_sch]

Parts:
C_CP1: 22nF 50V X7R; C_0603_1608Metric
C_CP2, C_CP3, C_CP4: 22 nF 50V X7R; C_0603_1608Metric
C_VCP1, C_VCP2, C_VCP3, C_VCP4: 100 nF 50V X7R; C_0603_1608Metric
C_VM1, C_VM2, C_VM3, C_VM4: 470 µF 50V electrolytic; CP_Radial_D10.0mm_P5.00mm
C_VM1_DEC1, C_VM2_DEC2, C_VM3_DEC3, C_VM4_DEC4: 100 nF 50V X7R; C_0603_1608Metric
J_M1, J_M2, J_M3, J_M4: Conn_01x02; TerminalBlock_Phoenix_MKDS-1,5-2-5.08_1x02_P5.08mm_Horizont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
LED_FAULT1, LED_FAULT2, LED_FAULT3, LED_FAULT4: LTST-C190KRKT Red; LED_0603_1608Metric
R_FAULT_LED1, R_FAULT_LED2, R_FAULT_LED3, R_FAULT_LED4: 1 kΩ 1% 0603; R_0603_1608Metric
R_FAULT_PU1, R_FAULT_PU2, R_FAULT_PU3, R_FAULT_PU4: 10 kΩ 1% 0603; R_0603_1608Metric
R_IMODE1, R_IMODE2, R_IMODE3, R_IMODE4: 20 kΩ 1% 0603; R_0603_1608Metric
R_IPROPI1, R_IPROPI2, R_IPROPI3, R_IPROPI4: 1 kΩ 1% 0603; R_0603_1608Metric
R_NSLEEP1, R_NSLEEP2, R_NSLEEP3, R_NSLEEP4: 100 kΩ 1% 0603; R_0603_1608Metric
U_M1, U_M2, U_M3, U_M4: DRV8874PWPR; SOP65P640X120-17N

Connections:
+3V3: R_FAULT_PU1.1, R_FAULT_PU2.1, R_FAULT_PU3.1, R_FAULT_PU4.1, R_NSLEEP1.1, R_NSLEEP2.1, R_NSLEEP3.1, R_NSLEEP4.1, U_M1.5 (VREF), U_M2.5 (VREF), U_M3.5 (VREF), U_M4.5 (VREF); also elsewhere on the board
/i2c_bus/IPROPI_M1: R_IPROPI1.1, U_M1.6 (IPROPI); also elsewhere on the board
/i2c_bus/IPROPI_M2: R_IPROPI2.1, U_M2.6 (IPROPI); also elsewhere on the board
/i2c_bus/IPROPI_M3: R_IPROPI3.1, U_M3.6 (IPROPI); also elsewhere on the board
/i2c_bus/IPROPI_M4: R_IPROPI4.1, U_M4.6 (IPROPI); also elsewhere on the board
/motor_dc/M1_DIR: U_M1.2 (PH/IN2); also elsewhere on the board
/motor_dc/M1_PWM: U_M1.1 (EN/IN1); also elsewhere on the board
/motor_dc/M2_DIR: U_M2.2 (PH/IN2); also elsewhere on the board
/motor_dc/M2_PWM: U_M2.1 (EN/IN1); also elsewhere on the board
/motor_dc/M3_DIR: U_M3.2 (PH/IN2); also elsewhere on the board
/motor_dc/M3_PWM: U_M3.1 (EN/IN1); also elsewhere on the board
/motor_dc/M4_DIR: U_M4.2 (PH/IN2); also elsewhere on the board
/motor_dc/M4_PWM: U_M4.1 (EN/IN1); also elsewhere on the board
/motor_dc/VMOT: C_VCP1.2, C_VCP2.2, C_VCP3.2, C_VCP4.2, C_VM1.1, C_VM1_DEC1.1, C_VM2.1, C_VM2_DEC2.1, C_VM3.1, C_VM3_DEC3.1, C_VM4.1, C_VM4_DEC4.1, U_M1.11 (VM), U_M2.11 (VM), U_M3.11 (VM), U_M4.11 (VM); also elsewhere on the board
GND: C_VM1.2, C_VM1_DEC1.2, C_VM2.2, C_VM2_DEC2.2, C_VM3.2, C_VM3_DEC3.2, C_VM4.2, C_VM4_DEC4.2, LED_FAULT1.1 (K), LED_FAULT2.1 (K), LED_FAULT3.1 (K), LED_FAULT4.1 (K), R_IMODE1.1, R_IMODE2.1, R_IMODE3.1, R_IMODE4.1, R_IPROPI1.2, R_IPROPI2.2, R_IPROPI3.2, R_IPROPI4.2, U_M1.16 (PMODE), U_M2.16 (PMODE), U_M3.16 (PMODE), U_M4.16 (PMODE); also elsewhere on the board
MGND: U_M1.9 (PGND), U_M1.15 (GND), U_M2.9 (PGND), U_M2.15 (GND), U_M3.9 (PGND), U_M3.15 (GND), U_M4.9 (PGND), U_M4.15 (GND); also elsewhere on the board
unnamed: J_M1.1, U_M1.8 (OUT1)
unnamed: J_M1.2, U_M1.10 (OUT2)
unnamed: J_M2.1, U_M2.8 (OUT1)
unnamed: J_M2.2, U_M2.10 (OUT2)
unnamed: J_M3.1, U_M3.8 (OUT1)
unnamed: J_M3.2, U_M3.10 (OUT2)
unnamed: J_M4.1, U_M4.8 (OUT1)
unnamed: J_M4.2, U_M4.10 (OUT2)
unnamed: LED_FAULT1.2 (A), R_FAULT_LED1.2
unnamed: LED_FAULT2.2 (A), R_FAULT_LED2.2
unnamed: LED_FAULT3.2 (A), R_FAULT_LED3.2
unnamed: LED_FAULT4.2 (A), R_FAULT_LED4.2
unnamed: C_CP1.1, U_M1.13 (CPH)
unnamed: C_CP1.2, U_M1.14 (CPL)
unnamed: R_IMODE1.2, U_M1.7 (IMODE)
unnamed: R_FAULT_LED1.1, R_FAULT_PU1.2, U_M1.4 (NFAULT)
unnamed: R_NSLEEP1.2, U_M1.3 (NSLEEP)
unnamed: C_VCP1.1, U_M1.12 (VCP)
unnamed: C_CP2.1, U_M2.13 (CPH)
unnamed: C_CP2.2, U_M2.14 (CPL)
unnamed: R_IMODE2.2, U_M2.7 (IMODE)
unnamed: R_FAULT_LED2.1, R_FAULT_PU2.2, U_M2.4 (NFAULT)
unnamed: R_NSLEEP2.2, U_M2.3 (NSLEEP)
unnamed: C_VCP2.1, U_M2.12 (VCP)
unnamed: C_CP3.1, U_M3.13 (CPH)
unnamed: C_CP3.2, U_M3.14 (CPL)
unnamed: R_IMODE3.2, U_M3.7 (IMODE)
unnamed: R_FAULT_LED3.1, R_FAULT_PU3.2, U_M3.4 (NFAULT)
unnamed: R_NSLEEP3.2, U_M3.3 (NSLEEP)
unnamed: C_VCP3.1, U_M3.12 (VCP)
unnamed: C_CP4.1, U_M4.13 (CPH)
unnamed: C_CP4.2, U_M4.14 (CPL)
unnamed: R_IMODE4.2, U_M4.7 (IMODE)
unnamed: R_FAULT_LED4.1, R_FAULT_PU4.2, U_M4.4 (NFAULT)
unnamed: R_NSLEEP4.2, U_M4.3 (NSLEEP)
unnamed: C_VCP4.1, U_M4.12 (VCP)

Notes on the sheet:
MOTOR 1
BULK CAPS
MOTOR 4
MOTOR 2
MOTOR 3
